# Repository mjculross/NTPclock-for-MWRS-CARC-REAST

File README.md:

Title:         NTP Dual Clock
Author:        (original) Bruce E. Hall, w8bh.net (Original Version)
               (current) RAHinsley (VK2ARH), MJCulross (KD5RXT)
Date:          (original) 13 Feb 2021
               (current) 25 Jun 2026
Hardware:      ESP32-S2-mini, with ILI9341 TFT display
Software:      Arduino IDE (currently 1.8.19) with additional board
               packages & libraries (details below)
Legal:         Copyright (c) 2021 Bruce E. Hall.
               Open Source under the terms of the MIT License.

Description:   Dual UTC/Local NTP Clock with TFT display. Time is refreshed via
               NTP (both) and/or GPS. Status indicator for time freshness &
               WiFi strength.

Rev History:   [ see the README.txt file for full revision history ]

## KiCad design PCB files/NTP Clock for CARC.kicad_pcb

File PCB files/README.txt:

This folder contains the files needed to get PCBs fabricated for the CARC v4 NTPclock kit.
The zip files have been successfully sent to JLCPCB.
The PCB files have been successfully sent to OshPark.

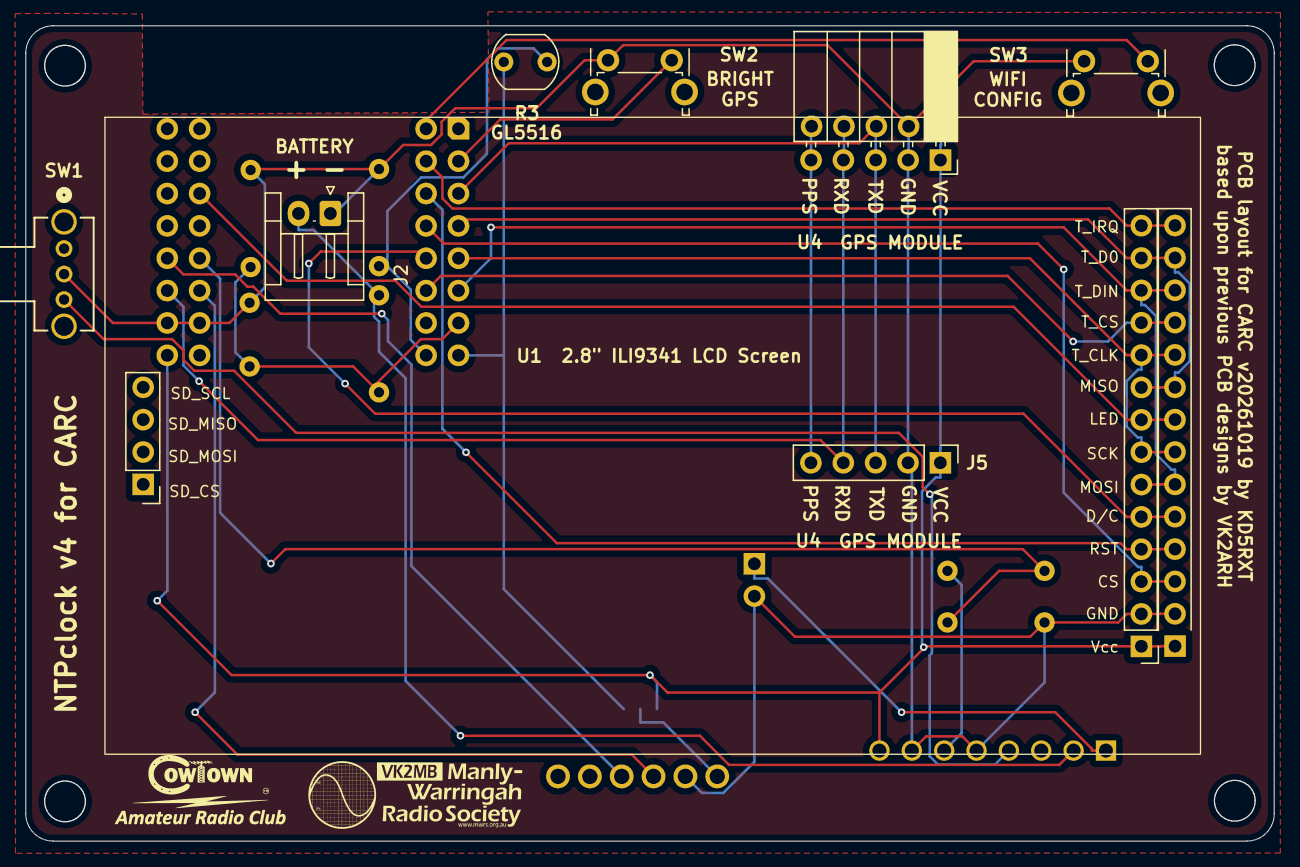
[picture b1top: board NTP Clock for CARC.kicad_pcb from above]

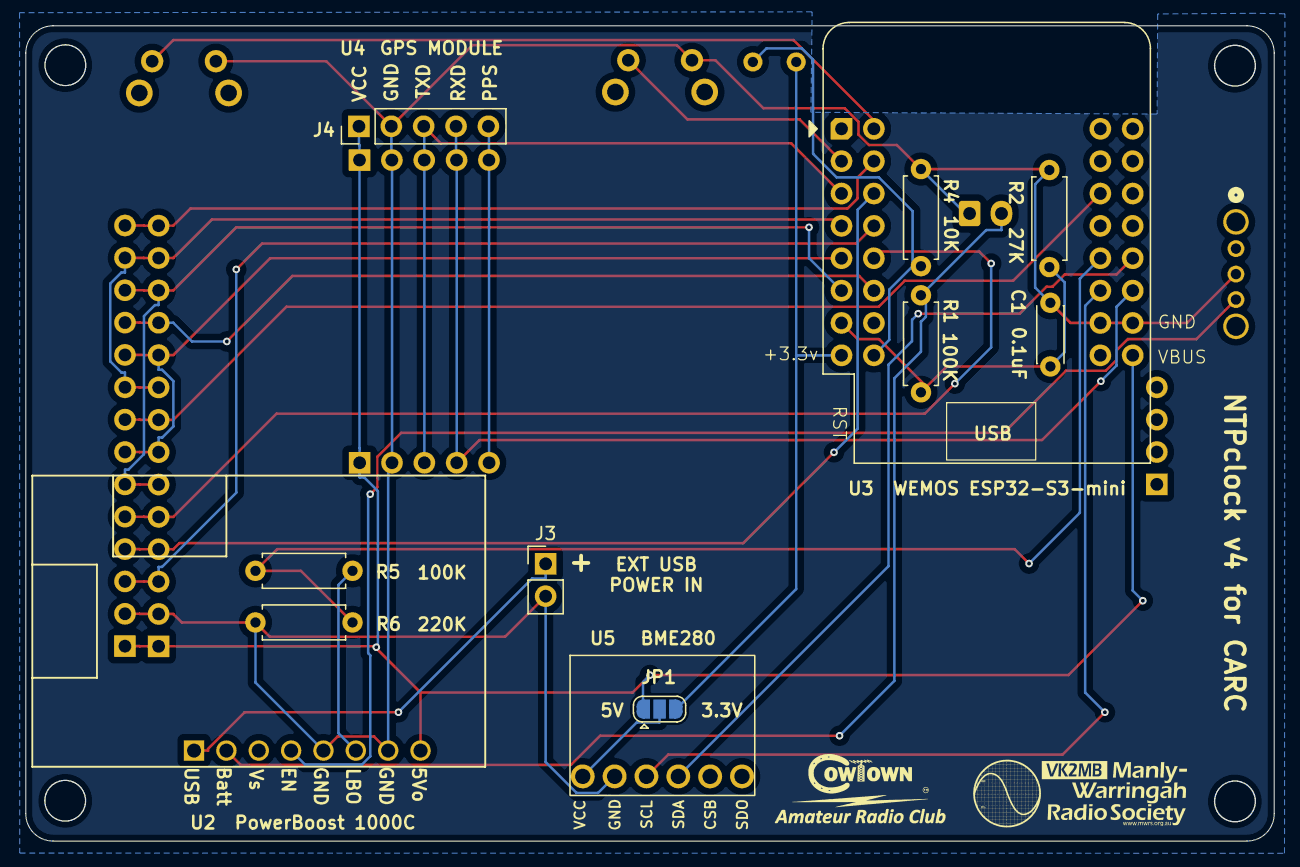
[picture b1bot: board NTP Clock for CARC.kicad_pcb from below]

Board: 2 copper layers, 98.0 x 64.0 mm, 29 parts (14 on the bottom side), 27 nets.

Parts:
C1: 0.1uF; C_Disc_D4.3mm_W1.9mm_P5.00mm
H1, H2, H3, H4: MountingHole; MountingHole_3.2mm_M3
J1: Conn_01x14; PinHeader_1x14_P2.54mm_Vertical
J2: BATTERY; JST_EH_S2B-EH_1x02_P2.50mm_Horizontal
J3: Conn_01x02_Pin; PinHeader_1x02_P2.54mm_Vertical
J4, J5: EXT_GPS; PinHeader_1x05_P2.54mm_Vertical
JP1: SolderJumper_3_Open; SolderJumper-3_P1.3mm_Open_RoundedPad1.0x1.5mm
R1, R5: 100K; R_Axial_DIN0207_L6.3mm_D2.5mm_P7.62mm_Horizontal
R2: 27K; R_Axial_DIN0207_L6.3mm_D2.5mm_P7.62mm_Horizontal
R3: GL5516; R_LDR_5.1x4.3mm_P3.4mm_Vertical
R4: 10K; R_Axial_DIN0207_L6.3mm_D2.5mm_P7.62mm_Horizontal
R6: 220K; R_Axial_DIN0207_L6.3mm_D2.5mm_P7.62mm_Horizontal
REF01, REF02: LOGO; CARC Logo Small
REF03, REF04: MWRS Logo Medium
SW1: OS102011MA1QN1; OS102011MA1QN1_CNK
SW2: BRIGHT / GPS; SW_Tactile_SPST_Angled
SW3: WIFI / CONFIG; SW_Tactile_SPST_Angled
U1: Teensy ILI9341; 2.8in LCD Display
U2: Powerboost1000C; PowerBoost1000C
U3: WEMOS_ESP32-S3-mini; WEMOS_S3_mini
U4: GT-U7; PinSocket_1x05_P2.54mm_Horizontal GPS
U5: BME280; BME280 Module

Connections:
+3.3V: JP1.3 (B), R3.1, U3.8 (+3.3v)
+5V: J1.1, J4.1, J5.1, JP1.1 (A), U1.1 (VCC), U2.8 (5Vo), U3.9 (VBUS), U4.1 (Vcc)
GNDREF: C1.2, J1.2, J2.1, J3.2, J4.2, J5.2, R2.2, R4.2, R6.2, SW1.2, SW2.1, SW3.1, U1.2 (GND), U2.5 (GND), U2.7 (G), U3.10 (GND), U3.26 (GND), U4.2 (Gnd), U5.2 (GND)
unnamed: J1.3, U1.3 (CS), U3.20 (IO06)
unnamed: J1.4, U1.4 (RESET), U3.19 (IO05)
unnamed: J1.5, U1.5 (DC), U3.21 (IO07)
unnamed: J1.8, U1.8 (LED), U3.30 (IO38)
unnamed: J1.7, J1.10, U1.7 (SCK), U1.10 (T_CLK), U3.5 (IO13)
unnamed: J1.11, U1.11 (T_CS), U3.22 (IO08)
unnamed: J1.6, J1.12, U1.6 (SDI(MOSI)), U1.12 (T_DIN), U3.6 (IO11)
unnamed: J1.9, J1.13, U1.9 (SDO(MISO)), U1.13 (T_DO), U3.4 (IO12)
unnamed: J1.14, U1.14 (T_IRQ), U3.18 (IO03)
unnamed: J3.1, U2.1 (USB)
unnamed: J4.3, J5.3, U3.3 (IO04), U4.3 (TXD)
unnamed: J4.4, J5.4, U3.11 (IO16), U4.4 (RXD)
unnamed: J4.5, J5.5, U4.5 (PPS)
unnamed: JP1.2 (C), U5.1 (VCC)
unnamed: J2.2, R1.1, U2.2 (BAT)
unnamed: SW1.3, U2.4 (EN)
unnamed: R5.1, U2.6 (LBO)
unnamed: SW3.2, U3.17 (IO01)
unnamed: SW2.2, U3.2 (IO02)
unnamed: C1.1, R1.2, R2.1, U3.7 (IO10)
unnamed: R3.2, R4.1, U3.24 (IO14)
unnamed: U3.27 (IO17), U5.3 (SCL)
unnamed: U3.12 (IO18), U5.4 (SDA)
unnamed: R5.2, R6.1, U3.28 (IO21)
